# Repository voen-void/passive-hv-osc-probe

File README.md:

# Passive High Voltage oscilloscope probe

> [!IMPORTANT]
> **UNTESTED.** This probe has not been built or measured yet. The voltage rating is a design target, and every performance figure below comes from simulation. Don't build it for real use until it has been tested.

A **1000:1 passive high-voltage probe** for a standard 1 MΩ oscilloscope input, designed for **up to 20 kV peak**. A compensated resistive/capacitive divider of 20 SMD segments is cast in polyurethane resin inside a grounded brass tube. The output is a BNC connector and a 1–3 m coax cable to the scope.

The design is backed by a set of [modelling tools](tools/README.md). They read the KiCad files directly and do the following:
- extract the parasitic capacitances with a 3D field solver;
- simulate the probe together with its cable and scope;
- size the compensation, design a graded divider, and map the electric-field stress.

| | |
|---|---|
| Attenuation | 1000:1 into 1 MΩ |
| Max. voltage (design target) | 20 kV peak |
| Divider, high side | 20 × (2 MΩ ∥ (graded 270…47 pF + 33 Ω)) |
| Flatness after compensation | ≈ 3 % from 10 Hz to 1 MHz |
| Bandwidth | ≈ 36 MHz (−3 dB), 22 MHz (±1 dB) |
| Rise time / overshoot (1 ns edge) | 8.7 ns / 11 % |
| Input impedance (DUT loading) | 40 MΩ ∥ 20 pF |
| Shield | brass tube, 27.6 mm ID, end cap at the BNC end |
| Potting | Huntsman Arathane CW 5620 BLUE |
| Status | **not built** |

The performance figures are simulated for 1.5 m RG58, a scope input of 1 MΩ ∥ 15 pF, the 49.9 Ω back termination (R29) and an ideal source at the tip, with the resin as measured on a cast sample ([assumptions](#assumptions-and-limits)).

> [!NOTE]
> The PCBs for this project have been provided by [PCBWay](https://www.pcbway.com/).

The design is based on an [EEVblog video](https://www.youtube.com/watch?v=jUvSP3BQpvs). The electrical design is done in [KiCad](https://www.kicad.org/) 10 and the mechanical design in [onshape](https://www.onshape.com/en/).

## Contents

- [How the probe works](#how-the-probe-works)
- [Design](#design)
- [Simulation results](#simulation-results)
- [Building it](#building-it)
- [Calibration](#calibration)
- [Safety](#safety)
- [Repository layout and tools](#repository-layout-and-tools)
- [Previous revision](#previous-revision)

## How the probe works

The basic idea is a voltage divider: a large resistance from the input to the output, and a small one from the output to ground.

<p align="center">
  <picture>
    <source media="(prefers-color-scheme: dark)" srcset="images/schematics/divider-dark.svg">
    
  </picture>
</p>

At high frequencies, every capacitance across the resistors and from the divider to its surroundings changes the division ratio. The resistors are therefore bypassed by capacitors, which take over at high frequency:

<p align="center">
  <picture>
    <source media="(prefers-color-scheme: dark)" srcset="images/schematics/divider-compensated-dark.svg">
    
  </picture>
</p>

The divider is **compensated** when the top and bottom halves have the same time constant: R_top·C_top = R_bottom·C_bottom. The division ratio is then independent of frequency.

Here the top half is 20 segments of 2 MΩ in series (40 MΩ). Splitting it this way keeps each part at about 1 kV at 20 kV DC. The bottom half is:
- **Resistors:** 56 kΩ ∥ (56 kΩ + RV2). RV2 is a 1 MΩ 10-turn trimmer that sets the exact DC ratio together with the scope's 1 MΩ.
- **Capacitors:** the compensation capacitors C34, C35 and the 5.5–65 pF trimmer C13, plus the cable, the scope input and the TVS diode D1.
- **Output:** R29 (49.9 Ω) back-terminates the cable, and D1 protects the scope input.

### Why stray capacitance dominates this design

The divider sits on a board inside a grounded tube full of resin. Every node between two segments therefore has a capacitance to the shield, C<sub>s</sub> in the diagram:

<p align="center">
  <picture>
    <source media="(prefers-color-scheme: dark)" srcset="images/schematics/divider-ladder-dark.svg">
    
  </picture>
</p>

The field solver puts it at about **1.37 pF per node at 1 MHz, 26 pF in total**, and 1.64 pF (31 pF) at 1 kHz, where the resin's permittivity is higher. The 20 capacitors on the board in series give only 6.0 pF.

At high frequency these strays pull current to ground before it reaches the bottom of the divider. Two things follow:
1. **Compensation can't fix it.** The error has the wrong shape, a broad dip between ~100 Hz and ~100 kHz, not just the wrong size. No bottom capacitance removes it.
2. **Fast edges concentrate on the HV end.** With uniform 47 pF capacitors, the first segment would carry 3.1× its DC share of a fast edge.

The fix is a **graded divider**. The capacitors are largest at the HV end and smaller towards the bottom, sized so the extra current through each one feeds exactly the stray capacitance below it. The tools compute the grading from the extracted capacitances.

## Design

Files:
- schematic: [PDF](images/kicad/schematic.pdf), [SVG](images/kicad/schematic.svg), source in [`hv-probe-passive/`](hv-probe-passive/);
- board layout with the shield and resin outlines: [SVG](images/kicad/layout.svg);
- assembly drawings: [top](images/kicad/assembly-top.pdf), [bottom](images/kicad/assembly-bottom.pdf).

### Construction

- **PCB:** 2-layer, 1.6 mm FR4, 1 oz copper, all parts on the bottom side. Each divider step is connected by a copper pour that stays inside the outline of its pads, with filleted corners and solid pad connections (zones `s0`…`s20`, drawn by [`tools/make_pours.py`](tools/README.md#copper-pours-make_pourspy)). Soldermask is removed where the board is potted. Slots and notches in the outline lengthen the creepage paths and let the resin flow through.
- **Shield:** brass tube, 27.6 mm inner diameter, 1 mm wall. It's drawn in cross-section on the **User.1** layer, together with the **end cap** that closes the BNC end. The tube must be grounded.
- **Resin:** [Huntsman Arathane CW 5620 BLUE](https://products.huntsman.com/products/arathane-cw-5620-hy-5610), drawn on **User.2**. It fills the tube from the start of the divider, and its rounded body continues beyond the tube around the HV end. The LV end with the trimmer and RV2 stays accessible.
- **HV terminal:** a machined brass piece soldered onto the tapered tip of the board (see [Building it](#building-it)).

### Divider capacitors and damping

Each of the 20 segments is a 2 MΩ resistor in parallel with a C0G capacitor and its 33 Ω damping resistor. The capacitors are graded (E12 values, 3 kV, 1808):

| segment | C14 | C15 | C16 | C17 | C18 | C19 | C20 | C21 | C22 | C23 |
|---|---|---|---|---|---|---|---|---|---|---|
| **C** | 270p | 270p | 270p | 270p | 270p | 270p | 270p | 270p | 220p | 220p |

| segment | C24 | C25 | C26 | C27 | C28 | C29 | C30 | C31 | C32 | C33 |
|---|---|---|---|---|---|---|---|---|---|---|
| **C** | 180p | 150p | 120p | 120p | 100p | 68p | 68p | 56p | 47p | 47p |

- **The values come from the tools:** the grading that gives the flattest response for the stray capacitances of this layout ([how](tools/README.md#graded-divider-and-its-optimiser)).
- **Nothing is above 270 pF,** because larger values are hard to source in 3 kV C0G 1808 (`[optimize] cap_max` in [`tools/probe.toml`](tools/probe.toml)). An unlimited grading would run from 470 pF down. With the limit, the values at the HV end stop at 270 pF and the middle of the divider is larger instead. That costs no flatness, but fast edges are split less evenly between the segments (worst segment 1.43 times its share, against 1.32).
- **The list is one of several that are equally good.** Lists that differ by one E12 step in a few places reach the same error, and stay within 2.9–3.3 % if the real stray capacitances are up to 10 % larger than modelled.
- **33 Ω per capacitor (R30–R49)** damps the ringing of the divider's own inductance; see [Damping](#damping).
- **Bottom capacitance:** C34 + C35 = 2.7 nF + 270 pF, for 1.5 m of RG58. Other cable lengths need other values; see [the table](#compensation-capacitor-per-cable-length).
- **Part tolerances barely touch the flatness, but they move the bottom capacitance.** With the tolerances of the parts chosen (1 to 10 %), 9 builds in 10 stay below 3.1 %. The bottom capacitance they need differs by about ±100 pF, more than the trimmer's ±30 pF, so expect to select C35 on the finished probe.

To recompute after any change: `python tools/run_all.py`, or for the response alone `python tools/probe_sim.py response --optimize` (add `--seg-r 22` to try another damping resistor).

### Bill of materials

| Reference | Qty | Value | Part |
|---|---|---|---|
| R7–R26 | 20 | 2 MΩ, 2512 | HV121WF2004T4E |
| C14–C21 | 8 | 270 pF C0G, 1808, 3 kV | 1808N271J302CT |
| C22, C23 | 2 | 220 pF C0G, 1808, 3 kV | 1808N221K302CT |
| C24 | 1 | 180 pF C0G, 1808, 3 kV | C1808C181FHGACAUTO |
| C25 | 1 | 150 pF C0G, 1808, 3 kV | 1808N151K302CT |
| C26, C27 | 2 | 120 pF C0G, 1808, 3 kV | 1808N121J302CT |
| C28 | 1 | 100 pF C0G, 1808, 3 kV | CC1808KKNPOEBN101 |
| C29, C30 | 2 | 68 pF C0G, 1808, 3 kV | 1808N680J302CT |
| C31 | 1 | 56 pF C0G, 1808 | 1808J5K00560KCT |
| C32, C33 | 2 | 47 pF C0G, 1808, 3 kV | FV42N470J302ECG |
| R30–R49 | 20 | 33 Ω, 1206 (damping) | CRCW120633R0JNEAHP |
| C34 | 1 | 2.7 nF C0G, 1206 | FM31N272J251EEG |
| C35 | 1 | 270 pF C0G, 1206 | CC1206JKNPOCBN271 |
| C13 | 1 | 5.5–65 pF trimmer | BFC280832659 |
| RV2 | 1 | 1 MΩ 10-turn | 3296X-1-105LF |
| R27, R28 | 2 | 56 kΩ, 0805 | 0805W8F5602T5E |
| R29 | 1 | 49.9 Ω, 0805 (back termination) | 0805W8F499JT5E |
| D1 | 1 | bidirectional TVS, ≈ 20 pF | H36VND3B |
| J2 | 1 | BNC, horizontal | Amphenol B6252HB-NPP3G-50 |
| – | – | resin, brass tube and end cap, 3D-printed mold | |

The schematic carries the supplier numbers for each part.

## Simulation results

All figures come from the [tools](tools/README.md) run on the current KiCad files; outputs are in [`tools/results/`](tools/results/). They predict an untested design: treat them as engineering estimates, not specifications.

### Extracted parasitics

| | value at 1 kHz |
|---|---|
| each divider node → shield | 1.62–1.71 pF (31.1 pF in total) |
| across each segment, parallel to its capacitor | 0.44–0.47 pF |
| HV tip → ground | 3.7 pF |
| divider bottom → ground | 4.3 pF |

These are evaluated at 1 kHz, where the resin's εr is 5.2. At 1 MHz (εr = 4.25) the node-to-shield total is 26.0 pF, at 10 Hz (εr = 6.5) it is 38.0 pF. A node comprises its two resistor pads, its capacitor and damping-resistor pads, the pour that joins them, and the pads between the next damping resistor and its capacitor. [Full table](tools/results/capacitance_summary.txt) · [how the board was imported](tools/results/model_check.png).

### Frequency and step response

| (1.5 m RG58) | value |
|---|---|
| gain error, 10 Hz – 1 MHz | ≈ 2.8 % |
| −3 dB / ±1 dB bandwidth | 36 MHz / 22 MHz |
| rise time / overshoot (1 ns edge) | 8.7 ns / 11 % |
| input capacitance | 20.1 pF |
| fast-edge voltage per segment | 0.70…1.43 × its DC share (max ≈ 1.43 kV at 20 kV) |

**The remaining 3 % is the resin.** Its permittivity falls from 6.5 at 10 Hz to 4.25 at 1 MHz, spread evenly over the whole band, and the stray capacitances follow it while the C0G capacitors do not. The error is +2.5 % near 900 Hz, −2.8 % near 6 kHz and back to +2.8 % at 1 MHz; no fixed set of capacitors and no bottom capacitance removes it. Getting below 3 % needs a potting compound with a loss tangent near 0.01 instead of 0.04–0.08, or a divider with less stray capacitance per node.

#### Damping

| resistor per capacitor | −3 dB | ±1 dB | rise | overshoot |
|---|---|---|---|---|
| 10 Ω | 78 MHz | 60 MHz | 0.9 ns | 115 % |
| 22 Ω | 49 MHz | 34 MHz | 5.0 ns | 29 % |
| **33 Ω (fitted)** | **36 MHz** | **22 MHz** | **8.7 ns** | **11 %** |
| 47 Ω | 26 MHz | 15 MHz | 12.5 ns | 5 % |
| 68 Ω | 18 MHz | 10 MHz | 19.3 ns | 3 % |

The fast current runs the 10.9 mm pitch of each segment with its return on the tube wall. That is about 6 nH per segment, 122 nH along the divider, plus about 45 nH for the strip to the tip: the divider behaves as an LC ladder of about 70 Ω, 1.8 ns long, and rings unless it is damped to match. A resistor at the tip also damps (47 Ω there with the 33 Ω fitted: 6 % overshoot, 32 MHz), but costs more bandwidth for the same damping.

These figures are for an ideal source at the tip and depend on inductances estimated from the geometry (±30 %), so check the step response of an assembled board in its tube before potting it. The lead and ground return to the circuit under test add about 1 nH per mm and will usually dominate; set `source_l` in [`tools/probe.toml`](tools/probe.toml) to see their effect. Above ~100 MHz the model is qualitative.

#### Divider options compared

- **Uniform capacitors** do not work in this tube: 220 pF in every segment still leaves 8.6 % error, at 21 pF input capacitance.
- **Grading** reaches 2.8–3.2 % at 18.5–20.1 pF.
- **Grading from 22 or 33 pF** at the bottom instead of 47 pF would load the DUT a little less (18.5 / 19.2 pF) for 3.2 / 3.1 % error, and need less bottom capacitance (1.2 / 2.0 nF).

### Compensation capacitor per cable length

The cable's capacitance (~100 pF/m) is part of the bottom capacitance, and the trimmer only covers ±1 % of it. **So the fixed capacitors have to match the cable you'll use.**

| RG58 length | C34 + C35 + C13 | e.g. |
|---|---|---|
| 1 m | 3.06 nF | 2.7 nF + 330 pF, trimmer ≈ 30 pF |
| **1.5 m (fitted)** | 3.01 nF | 2.7 nF + 270 pF, trimmer ≈ 40 pF |
| 2 m | 2.96 nF | 2.7 nF + 220 pF, trimmer ≈ 40 pF |
| 3 m | 2.86 nF | 2.7 nF + 120 pF, trimmer ≈ 40 pF |

These assume a 15 pF scope input and 20 pF for D1. `python tools/probe_sim.py optimize` recomputes them; use `--c-scope` and `--length` for your setup.

### Electric-field stress

At 20 kV, with the divider compensated, the highest fields are at the HV end of the divider, at the edge of the HV pour that faces the tube wall just inside the tube mouth (x ≈ 278 mm):

| | peak at copper edges | bulk | short-term strength |
|---|---|---|---|
| resin | 10.7 kV/mm | 8.3 kV/mm | 25 kV/mm |
| FR4 | 11.1 kV/mm | 7.9 kV/mm | ~20 kV/mm |
| along the board surface (tangential) | 7.5 kV/mm | | |

- **The HV pour is larger than its pads, and the strip to the tip is 2.5 mm wide.** The first resistor and damping resistor sit in the tube mouth. A pour flush with their pads and a 1 mm strip would put 10.7 kV/mm into the resin at the end of the damping resistor. Growing the pour by 1 mm towards the tip and the tube wall brings that to 8.4 kV/mm on the same grid, for 0.3 pF more input capacitance ([tools README](tools/README.md#copper-pours-make_pourspy)).
- **Along the divider** the pours that connect each step lower the resin field by about 10 % against bare pads, because they remove the gaps between the pads, for 5 % more capacitance to the shield. They stay inside the pads' outline, so the copper comes no closer to the shield or to the next step than the pads do (2.42 mm between adjacent steps).
- **The exposed tip in air** reaches ≈ 6.5 kV/mm in the model, above the ~3 kV/mm at which air breaks down. The brass terminal there must have large, smooth radii, and the real value depends on its shape and on the surroundings.

#### Reading the stress numbers

The "short-term strength" column is the datasheet breakdown of a thick, void-free sample, so comparing with it says little about whether the probe will last. What limits a potted HV part is **partial discharge (PD)**: small discharges in gas voids, along delaminated interfaces or at sharp edges. Each one is harmless, but repeated discharges erode the resin until it fails, sometimes after hours, sometimes after years.

- **Voids see more field than the resin around them.** The field in a gas void is εr times the resin field for a thin, flat void across the field, and 3εr/(2εr + 1) ≈ 1.3–1.4 times for a round one. Air in a 0.1 mm gap breaks down at about 8–9 kV/mm, and in a 50 µm gap at about 11 kV/mm. At the predicted bulk field of ~8.3 kV/mm, **any void of ~50–100 µm or larger near the HV end of the divider will discharge**, and a flat one far smaller. The casting has to be void-free there: degas the resin, cast under vacuum if possible, and pour slowly from the bottom.
- **Interfaces are weaker than the bulk.** The board surface sees 7.5 kV/mm along it, at the FR4–resin interface. Flux residue, moisture or poor adhesion turns that interface into a discharge or tracking path. Clean and dry the board before casting.
- **The copper-edge "peak" values are lower bounds.** A 35 µm copper edge has a radius of tens of µm, and the real field there is much higher than any grid cell can show. It is also where resin most easily fails to wet or pulls away from the board.
- **DC is different.** At DC the field between the materials divides by their conductivity, not their permittivity, and that isn't modelled. The DC map shows the distribution just after the voltage is applied. Under steady DC, discharges in voids are much rarer than under AC or repeated pulses.
- **Design target.** Cast-resin HV designs typically keep the working stress at a few kV/mm. The ~8.3 kV/mm here is acceptable only for short exposures and a void-free casting. Lowering it further (a flared or rolled tube rim, a tube that ends a few mm earlier, more distance between the first parts and the tube mouth) adds real margin. A partial-discharge test at above the working voltage is the only way to know. Even without a PD meter, discharges show up as small spikes on the probe output while a slowly rising DC or a 50 Hz voltage is applied.

### Where should the tube end?

Extending the tube past the divider doesn't lower the stress; it raises it. Over the bare HV conductor, the tube forms a coax with the full 20 kV between the inner conductor and nearby ground.

The shielding, meanwhile, improves exponentially with tube length (about 1.6× per 2.5 mm), so a tube that ends at the divider is already plenty:

| tube end | bulk stress (resin) | pickup at 1 MHz, tip-referred |
|---|---|---|
| 268 mm (12 mm before the end of the divider) | 6.4 kV/mm | 0.49 mV per V on the surroundings |
| 273 mm | 6.5 kV/mm | 0.21 mV/V |
| 278 mm | 6.7 kV/mm | 0.08 mV/V |
| **279.4 mm (current)** | ≈ 6.9 kV/mm | ≈ 0.055 mV/V |
| 283 mm | 7.3 kV/mm | 0.024 mV/V |
| 290.5 mm | 7.5 kV/mm | 0.004 mV/V |

The current row is interpolated between the swept positions. The sweep runs on a coarser grid (scale 1.3) than the stress table above, so compare its rows with each other, not with that table.

**The tube ends at 279.4 mm**, 1 mm short of the last divider pads (280.4 mm). Even there, 1 kV of nearby 1 MHz interference looks like 55 mV at the tip. Ending it 6 mm earlier (273 mm) would lower the bulk stress by about 6 % for 4× more pickup, which is still small; past 285 mm nothing is gained and the stress is 6–9 % higher. A larger gain would need a rounded or flared tube rim.

### Assumptions and limits

- **Resin dielectric.** A cast sample was measured on an RLC bridge from 20 Hz to 200 kHz and corrected with a C0G reference capacitor; 200 Hz–120 kHz is usable and consistent with Kramers–Kronig. The model is a Cole–Cole relaxation fitted to it ([tools README](tools/README.md#resin-measurement)): εr = 6.0 at 50 Hz, 5.2 at 1 kHz, 4.4 at 100 kHz and 4.25 at 1 MHz, with tanδ falling from 0.078 to 0.025. Three things are still open:
  - **the scale.** The sample is an uneven layer, 1 to 4 mm thick, so the datasheet's εr = 6 at 50 Hz fixes the scale. The sample's dimensions agree with that within about 10 %. Its shape over frequency and its loss do not depend on the thickness;
  - **air under the foil electrodes.** There are signs of some. It would mean the true loss and dispersion are about 30 % larger than read (εr = 3.8 at 1 MHz). The sample's dimensions lean against it without excluding it. The best capacitor list would differ in one value by one step (C31), and with the list as fitted the remaining error would be 3.4 % instead of 2.8 %;
  - **above 120 kHz** the model is an extrapolation. The bandwidth figures rest on it.

  Thickness readings at a dozen points under the electrodes, or a flat sample, would settle the first two; a VNA sweep of the sample to 100 MHz the third. No new field solve is needed.
- **Inductance.** Each segment's series inductance and the tip strip's are estimated from the geometry (6 nH and 45 nH), without magnetic coupling between segments. They set the overshoot and the damping needed, and are good to perhaps ±30 %. The overshoot also depends on the inductance of the bottom capacitors C34 and C35, taken as 0.74 nH each: 4 % with half of that, 23 % with twice.
- **Validity.** The circuit model is quasi-static and lumped: right in shape to ~100 MHz, qualitative above.
- **Field solver.** With grid lines on the pad edges, nominally identical steps agree within 1.5 % (most within 0.2 %) and the capacitances change by 2 % between the two finest grids that fit this machine; they are probably still a few percent low. The circuit model's scaling of the parasitics with permittivity is within 0.4 % of direct field solves over 10 Hz–100 MHz.
- **Checks.** The circuit model matches LTspice to 0.001 dB below 1 MHz and 0.05 dB at 30 MHz on the same netlist.
- **Not modelled:** the brass tip terminal, the input fuse, the connection to the circuit under test, part bodies (treated as resin), voids in the potting.

## Building it

### PCB

The board is a simple two-layer design:
- **Soldermask** is removed where the board will be potted. The part with soldermask stays outside the resin, so the compensation trimmer and RV2 can be adjusted afterwards.
- **A ground pad** is exposed for connecting the shield and end cap.

At the HV end, a large exposed copper area sits far from the shield to increase creepage distance. This tapered end sticks out of the tube and is cast in resin, preferably ribbed for even more creepage.

Before casting:
- **Machine a brass piece** that fits over the straight tip of the tapered end, with a female thread at its end. A screw threaded into it makes the HV contact.
- **Solder it to the tip.** Give it large, smooth radii (see [stress](#electric-field-stress)).

**Never apply excessive force** to the terminal relative to the probe body. The exposed part can be shaped to take a wrench, so you can hold the terminal while fastening an attachment. Tighten finger-tight only.

### Components

- **All divider capacitors must be C0G/NP0.** Class II dielectrics (X7R and similar) lose much of their capacitance under DC bias and with temperature, which would ruin the compensation.
- **The HV resistors** are 2512 high-voltage types.
- **Clean the board thoroughly** before casting; flux residue under the resin is a long-term breakdown path.

### Casting in resin

A 3D-printable mold has been designed in [onshape](https://cad.onshape.com/documents/634b2c7804eb6959816cbee4/w/1f30c7d8f223e5e8fad3fc6d/e/e251d38d61b503254921d7bb) (STL and PDF in [`mold/`](mold/)).

- **Mold material:** PETG releases well from the resin. The two halves are held together by 18 M4 × 70 mm bolts, and wax works as a release agent.
- **Pouring:** pour the resin into the metal tube with the tip of the probe facing down. Fill until it reaches the 3 mm vent holes at the top.
- **No bubbles:** degas the resin; trapped air is where breakdown starts.

## Calibration

Always calibrate with the cable and scope you'll use:

1. Fit C34 + C35 for your cable length (table above, or `probe_sim.py optimize`).
2. Set RV2 to about 110 kΩ, which gives 1000:1 into 1 MΩ (`probe_sim.py info` prints the exact value). Then trim RV2 for exactly 1000:1 with a known DC or low-frequency voltage.
3. Apply a square wave of a few hundred Hz to a few kHz and adjust C13 for the flattest top.
4. Check the response at several frequencies and with a fast edge.

## Safety

> [!CAUTION]
> High voltage can easily be lethal. Only work with it if you are qualified. You build and use this project at your own risk. This is experimental high-voltage equipment.

1. Don't use the probe on energized equipment unless you are qualified to work with high voltage.
2. 20 kV is a design target, not a verified rating.
3. Never rely on the probe alone for isolation.
4. Use a current-limited HV source for testing.
5. Make sure the oscilloscope and everything connected to it are rated appropriately. The scope ground is tied to mains protective earth and must stay that way during measurements. Remote control of the scope is recommended.
6. The shield must be properly grounded.
7. Inspect the probe for damage before every use.
8. Don't use a probe that has had an internal arc-over.
9. Potting makes internal faults hard or impossible to inspect.
10. Fast edges stress the divider unevenly (see [simulation](#frequency-and-step-response)); derate for pulsed or switching measurements.

The final breakdown voltage depends on the craftsmanship: the resin, the cleanliness of the parts when cast, and above all **no trapped air bubbles**. Keep a generous safety margin.

### Internal arc-over protection

For extra safety, put a **fuse in series with the probe input**. An internal arc-over would draw large current from a DUT that can supply it. Sustained arcing inside a hard-potted body can build pressure, and in an extreme case the probe could burst.

Microwave-oven fuses are the highest-voltage fuses that are cheaply available. Lower-current fuses would be better, but they are only rated to about 250 VAC.

**If the fuse ever blows, mark the probe as faulty and stop using it.**

## Repository layout and tools

| path | contents |
|---|---|
| [`hv-probe-passive/`](hv-probe-passive/) | KiCad project (schematic, PCB) |
| [`tools/`](tools/README.md) | field solver, circuit simulator, design scripts, [results](tools/results/) |
| [`images/kicad/`](images/kicad/) | renders and drawings generated from the KiCad files |
| [`images/schematics/`](images/schematics/) | the circuit diagrams of this page, drawn by `tools/draw_schematics.py` |
| [`mold/`](mold/) | casting mold (STL, drawing) |
| [`images/previous-revision/`](images/previous-revision/) | images of the through-hole revision |

After changing the design:

```
cd tools
python make_pours.py       # only after moving divider parts: redraw the copper pours, refill the zones (KiCad closed)
python run_all.py          # re-run all analyses (~15 min; --quick for a coarse check)
python render_kicad.py     # regenerate the images in images/kicad/
python draw_schematics.py  # redraw the circuit diagrams with the values on the board
```

## Previous revision

The first revision used five 10 MΩ axial HV resistors with 22 pF disc capacitors. I had it manufactured by PCBWay: I uploaded the gerbers, placed a quick order, and the five boards arrived within a couple of days. The packing and the board quality were excellent.

Its renders, assembly and dimension drawings are in [`images/previous-revision/`](images/previous-revision/), and its gerbers and BOM are in `hv-probe-passive/production/`. At the time, one probe cost about 99 USD in parts, without shipping: PCB 4.2, capacitors 32.8, BNC 8.2, resistors 7.1, trimmer 2.5, resin 25, tube 17, filament 2. The PCBs, the resin and the tube only come in larger quantities than one probe needs.

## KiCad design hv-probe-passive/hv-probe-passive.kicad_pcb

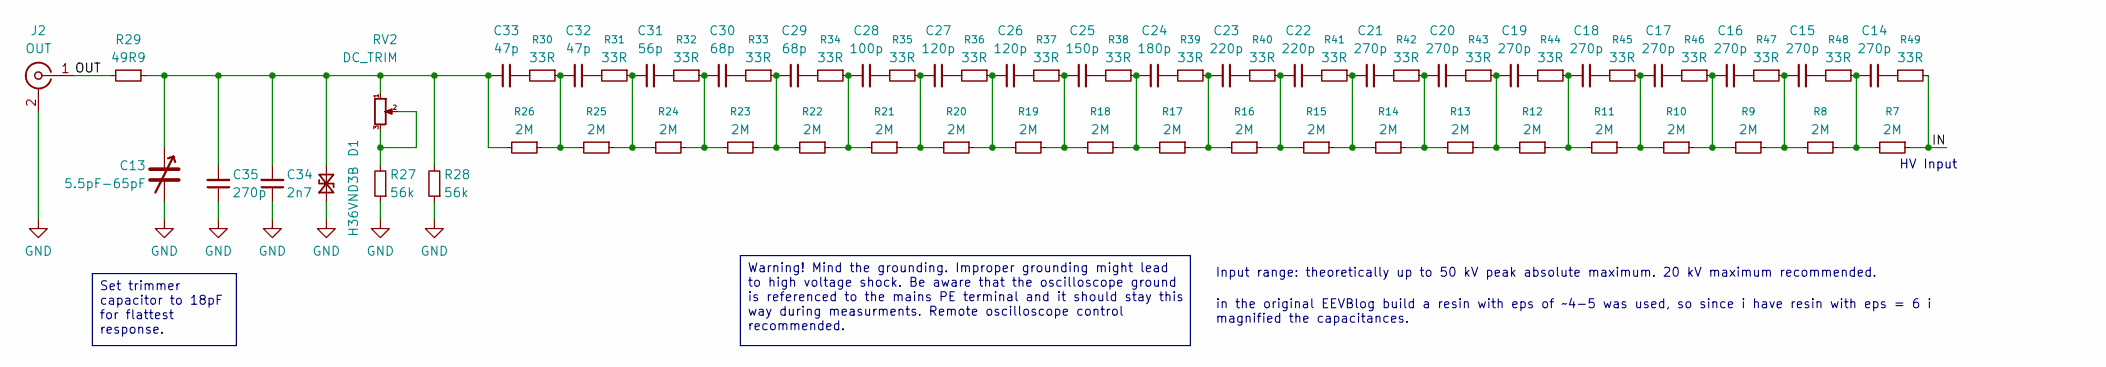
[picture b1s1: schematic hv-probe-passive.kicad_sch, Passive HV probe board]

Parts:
C13: 5.5pF-65pF; BFC2808 P5.0x7.5mm; MPN BFC280832659; LCSC C3273327
C14, C15, C16, C17, C18, C19, C20, C21: 270p; C_1808_4520Metric; MPN 1808N271J302CT; LCSC C3898309
C22, C23: 220p; C_1808_4520Metric; MPN 1808N221K302CT; LCSC C3893923
C24: 180p; C_1808_4520Metric; MPN C1808C181FHGACAUTO; LCSC C1883431
C25: 150p; C_1808_4520Metric; MPN 1808N151K302CT; LCSC C3888906
C26, C27: 120p; C_1808_4520Metric; MPN 1808N121J302CT; LCSC C3895824
C28: 100p; C_1808_4520Metric; MPN CC1808KKNPOEBN101; LCSC C1855551
C29, C30: 68p; C_1808_4520Metric; MPN 1808N680J302CT; LCSC C3895882
C31: 56p; C_1808_4520Metric; MPN 1808J5K00560KCT; LCSC C2351436
C32, C33: 47p; C_1808_4520Metric; MPN FV42N470J302ECG; LCSC C2958815
C34: 2n7; C_1206_3216Metric; MPN FM31N272J251EEG; LCSC C5632237
C35: 270p; C_1206_3216Metric; MPN CC1206JKNPOCBN271; LCSC C113874
D1: H36VND3B; D_SOD-323; MPN H36VND3B; LCSC C20615816
J2: OUT; BNC_Amphenol_B6252HB-NPP3G-50_Horizontal; MPN 112413
R7, R8, R9, R10, R11, R12, R13, R14, R15, R16, R17, R18, R19, R20, R21, R22, R23, R24, R25, R26: 2M; R_2512_6332Metric; MPN HV121WF2004T4E; LCSC C2779442
R27, R28: 56k; R_0805_2012Metric; MPN 0805W8F5602T5E; LCSC C17756
R29: 49R9; R_0805_2012Metric; MPN 0805W8F499JT5E; LCSC C17720
R30, R31, R32, R33, R34, R35, R36, R37, R38, R39, R40, R41, R42, R43, R44, R45, R46, R47, R48, R49: 33R; R_1206_3216Metric; MPN CRCW120633R0JNEAHP; LCSC C3009337
RV2: DC_TRIM; Potentiometer_Bourns_3296X_Horizontal; MPN 3296X-1-105LF; LCSC C49190482

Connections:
/IN: R7.1, R49.1
/OUT: J2.1 (In), R29.2
GND: C13.2, C34.1, C35.1, D1.1 (A1), J2.2 (Ext), R27.1, R28.1
unnamed: C14.1, R49.2
unnamed: C14.2, R7.2, R8.1, R48.1
unnamed: C15.1, R48.2
unnamed: C15.2, R8.2, R9.1, R47.1
unnamed: C16.1, R47.2
unnamed: C16.2, R9.2, R10.1, R46.1
unnamed: C17.1, R46.2
unnamed: C17.2, R10.2, R11.1, R45.1
unnamed: C18.1, R45.2
unnamed: C18.2, R11.2, R12.1, R44.1
unnamed: C19.1, R44.2
unnamed: C19.2, R12.2, R13.1, R43.1
unnamed: C20.1, R43.2
unnamed: C20.2, R13.2, R14.1, R42.1
unnamed: C21.1, R42.2
unnamed: C21.2, R14.2, R15.1, R41.1
unnamed: C22.1, R41.2
unnamed: C22.2, R15.2, R16.1, R40.1
unnamed: C23.1, R40.2
unnamed: C23.2, R16.2, R17.1, R39.1
unnamed: C24.1, R39.2
unnamed: C24.2, R17.2, R18.1, R38.1
unnamed: C25.1, R38.2
unnamed: C25.2, R18.2, R19.1, R37.1
unnamed: C26.1, R37.2
unnamed: C26.2, R19.2, R20.1, R36.1
unnamed: C27.1, R36.2
unnamed: C27.2, R20.2, R21.1, R35.1
unnamed: C28.1, R35.2
unnamed: C28.2, R21.2, R22.1, R34.1
unnamed: C29.1, R34.2
unnamed: C29.2, R22.2, R23.1, R33.1
unnamed: C30.1, R33.2
unnamed: C30.2, R23.2, R24.1, R32.1
unnamed: C31.1, R32.2
unnamed: C31.2, R24.2, R25.1, R31.1
unnamed: C32.1, R31.2
unnamed: C32.2, R25.2, R26.1, R30.1
unnamed: C33.1, R30.2
unnamed: C13.1, C33.2, C34.2, C35.2, D1.2 (A2), R26.2, R28.2, R29.1, RV2.1
unnamed: R27.2, RV2.2, RV2.3

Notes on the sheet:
HV Input
in the original EEVBlog build a resin with eps of ~4-5 was used, so since i have resin with eps = 6 i magnified the capacitances.
Set trimmer capacitor to 18pF for flattest response.
Warning! Mind the grounding. Improper grounding might lead to high voltage shock. Be aware that the oscilloscope ground is referenced to the mains PE terminal and it should stay this way during measurments. Remote oscilloscope control recommended.
Input range: theoretically up to 50 kV peak absolute maximum. 20 kV maximum recommended.

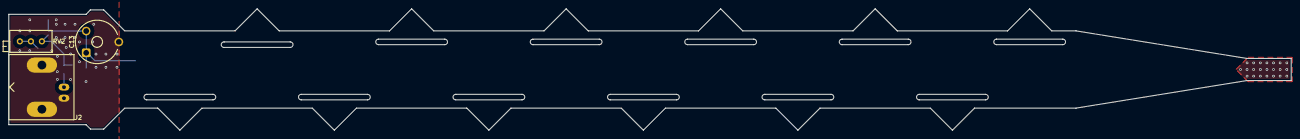
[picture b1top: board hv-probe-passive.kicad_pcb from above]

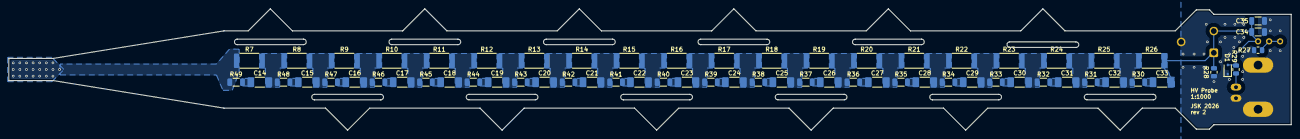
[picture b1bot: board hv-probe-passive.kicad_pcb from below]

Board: 2 copper layers, 295.1 x 27.9 mm, 69 parts (66 on the bottom side), 44 nets.

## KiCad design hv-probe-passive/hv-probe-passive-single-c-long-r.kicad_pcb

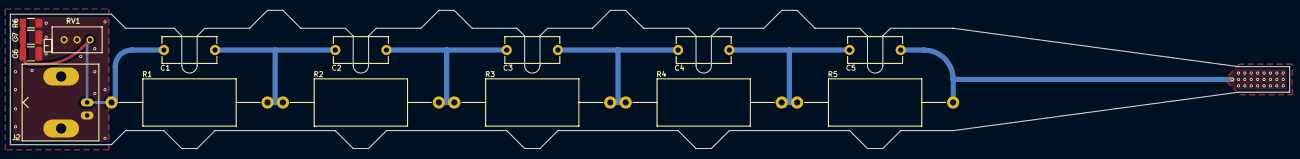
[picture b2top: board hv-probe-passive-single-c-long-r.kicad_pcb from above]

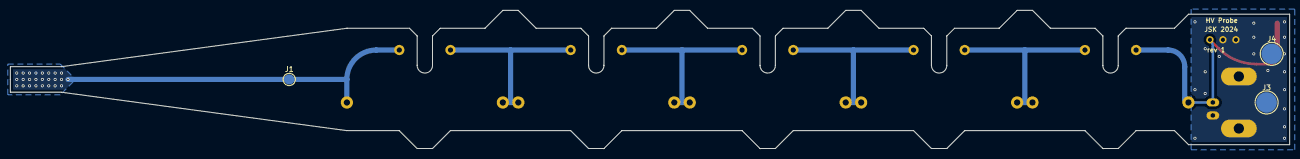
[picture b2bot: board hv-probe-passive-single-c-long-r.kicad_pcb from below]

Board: 2 copper layers, 250.0 x 27.0 mm, 18 parts (3 on the bottom side), 7 nets.

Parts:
C1, C2, C3, C4, C5: 22p; C_Disc_D10.5mm_W5.0mm_P10.00mm
C6, C7: 2n2; C_1210_3225Metric_Pad1.33x2.70mm_HandSolder
J1: IN; TestPoint_Pad_D2.0mm
J2: OUT; BNC_Amphenol_B6252HB-NPP3G-50_Horizontal
J3, J4: GND; TestPoint_Pad_D4.0mm
R1, R2, R3, R4, R5: 10M; R_Axial_DIN0918_L18.0mm_D9.0mm_P30.48mm_Horizontal
R6: 56k; C_1206_3216Metric_Pad1.33x1.80mm_HandSolder
RV1: TRIM; Potentiometer_Bourns_3296X_Horizontal

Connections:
GND: C6.1, C7.1, J2.2 (Ext), J3.1, J4.1, R6.1, RV1.2, RV1.3
unnamed: C1.2, C2.1, R1.2, R2.1
unnamed: C2.2, C3.1, R2.2, R3.1
unnamed: C3.2, C4.1, R3.2, R4.1
unnamed: C4.2, C5.1, R4.2, R5.1
unnamed: C5.2, J1.1, R5.2
unnamed: C1.1, C6.2, C7.2, J2.1 (In), R1.1, R6.2, RV1.1

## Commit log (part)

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2024-11-20 Update README.md
    first update
2024-11-20 added kicad project files
2024-11-21 rearrange README.md
    minor rearrangement
2024-11-21 added 2 images to the documentation
2024-11-21 made information on the schematic consistent with that in the readme
2024-11-21 expanded the readme
2024-11-21 updated renderings of the pcb and the schematic
2024-12-08 added a script for rough estimation of internal capacitance, corrected schematic
2024-12-09 restoring the readme, small updates to its content
2024-12-09 expanded the warnings in the readme, added a note on pcbway sponsorship
2025-01-05 added rendered images of the pcb to the repo
2025-01-05 improvements to the capacitance estimation script, the outputs have been made more readable and comments have been added to explain the reasoning behind it.
2025-01-05 additional info about possible capacitor replacements for the hv divider
